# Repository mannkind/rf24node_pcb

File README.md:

RF24Node-PCB
============

A low power sensor node PCB design (RF24L01+, DS18B20, etc)

# Notice - Unmaintained

Unmaintained; I discovered [MeanPenguin PCB](http://forum.mysensors.org/topic/408/eagle-files-for-a-meanpenguin-mysensors-pcb). That PCB utilizes cheaper Arduino Pro Mini clones and does everything I need it to do.

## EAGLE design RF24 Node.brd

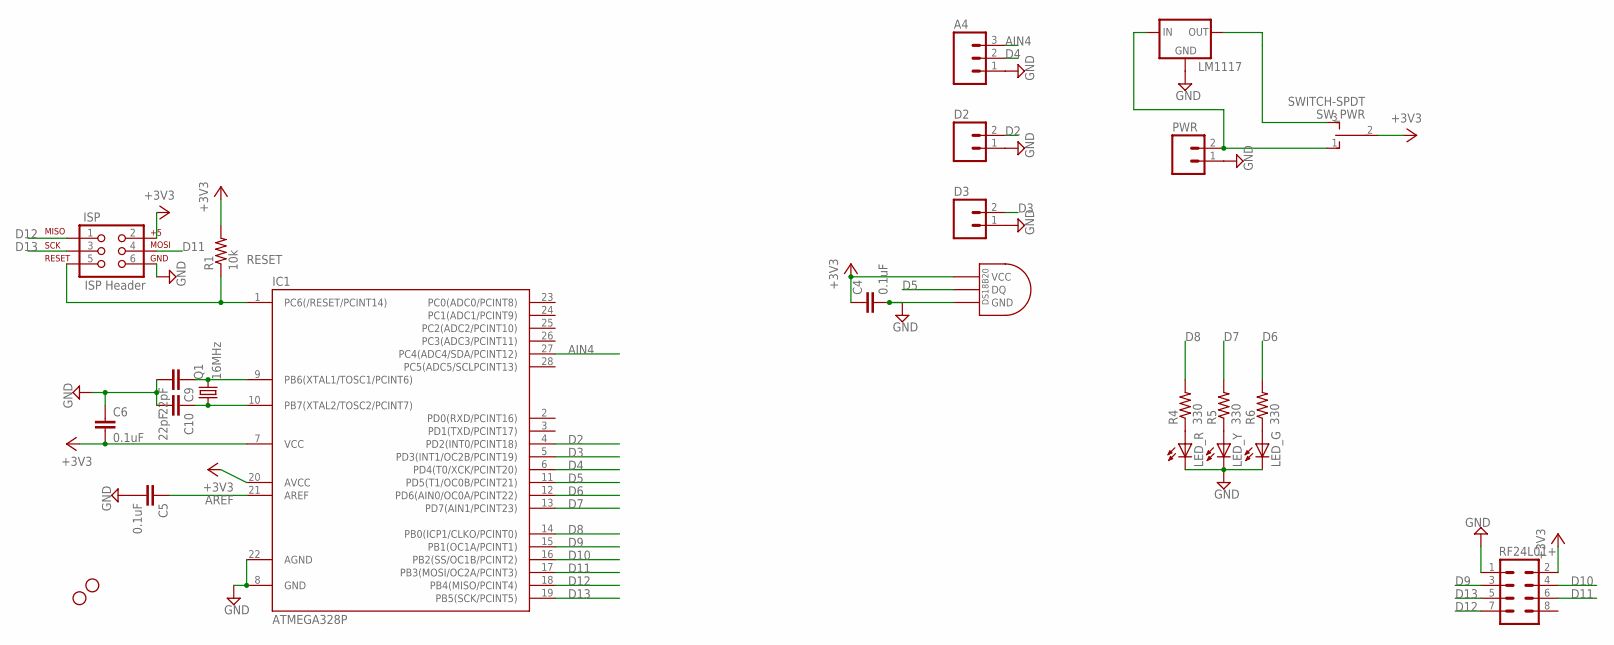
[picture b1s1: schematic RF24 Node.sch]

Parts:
A4: M03PTH; 1X03
C4, C5, C6: 0.1uF; C025-025X050
C9, C10: 22pF; C025-025X050
D2, D3: M02PTH; 1X02
DS18B20: DS1820TO92; DS1820
IC1: ATMEGA328P; DIL28-3
ISP: ISP Header; 2X3
JP2, JP8: STAND-OFF
LED_G: LED3MM
LED_R: LED3MM
LED_Y: LED3MM
LM1117: LM1117T-3.3-V; TO220V
PWR: M02PTH; 1X02
Q1: 16MHz; HC49/S
R1: 10k; 0204V
R4, R5, R6: 330; 0204V
RF24L01+: M04X2; 2X4
SW_PWR: SWITCH-SPDT; OS102011MS2QN1

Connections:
+3V3: C4.1, C6.2, DS18B20.VDD (VCC), IC1.7 (VCC), IC1.20 (AVCC), ISP.2, R1.2, RF24L01+.2, SW_PWR.2
AIN4: A4.3, IC1.27 (PC4(ADC4/SDA/PCINT12))
AREF: C5.1, IC1.21 (AREF)
D2: D2.2, IC1.4 (PD2(INT0/PCINT18))
D3: D3.2, IC1.5 (PD3(INT1/OC2B/PCINT19))
D4: A4.2, IC1.6 (PD4(T0/XCK/PCINT20))
D5: DS18B20.DQ, IC1.11 (PD5(T1/OC0B/PCINT21))
D6: IC1.12 (PD6(AIN0/OC0A/PCINT22)), R6.2
D7: IC1.13 (PD7(AIN1/PCINT23)), R5.2
D8: IC1.14 (PB0(ICP1/CLKO/PCINT0)), R4.2
D9: IC1.15 (PB1(OC1A/PCINT1)), RF24L01+.3
D10: IC1.16 (PB2(SS/OC1B/PCINT2)), RF24L01+.4
D11: IC1.17 (PB3(MOSI/OC2A/PCINT3)), ISP.4, RF24L01+.6
D12: IC1.18 (PB4(MISO/PCINT4)), ISP.1, RF24L01+.7
D13: IC1.19 (PB5(SCK/PCINT5)), ISP.3, RF24L01+.5
EXTPWR: LM1117.3 (IN), PWR.2, SW_PWR.1 (O)
GND: A4.1, C4.2, C5.2, C6.1, C9.2, C10.2, D2.1, D3.1, DS18B20.GND, IC1.8 (GND), IC1.22 (AGND), ISP.6, LED_G.K (C), LED_R.K (C), LED_Y.K (C), LM1117.1 (GND), PWR.1, RF24L01+.1
unnamed: LM1117.2 (OUT), SW_PWR.3 (S)
unnamed: LED_R.A, R4.1
unnamed: LED_Y.A, R5.1
unnamed: LED_G.A, R6.1
RESET: IC1.1 (PC6(/RESET/PCINT14)), ISP.5, R1.1
XTAL1: C9.1, IC1.9 (PB6(XTAL1/TOSC1/PCINT6)), Q1.2
XTAL2: C10.1, IC1.10 (PB7(XTAL2/TOSC2/PCINT7)), Q1.1

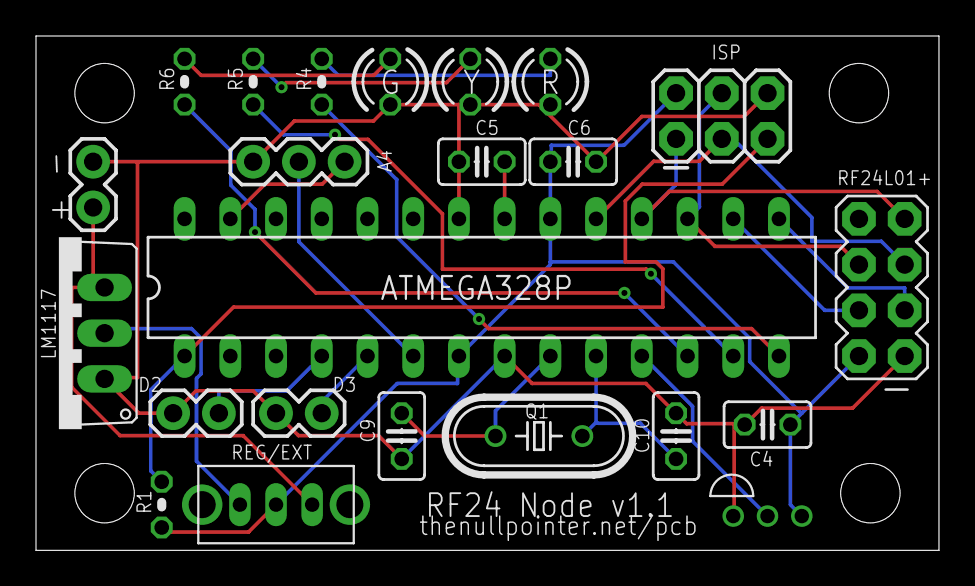
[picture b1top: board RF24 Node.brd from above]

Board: 2 copper layers, 50.2 x 28.6 mm, 27 parts (0 on the bottom side), 24 nets.

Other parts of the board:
JP1, JP9: STAND-OFF

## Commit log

2014-02-19 RF24 Node v1.2
2014-02-19 RF24 Node 1.3
2014-02-19 RF24 Node v1.1
2014-02-19 Adding license
2015-11-12 Update README.md
    Adding unmaintained notice

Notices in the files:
parts and their libraries:
SparkFun-Connectors: Licensing: CC v3.0 Share-Alike You are welcome to use this library for commercial purposes.
